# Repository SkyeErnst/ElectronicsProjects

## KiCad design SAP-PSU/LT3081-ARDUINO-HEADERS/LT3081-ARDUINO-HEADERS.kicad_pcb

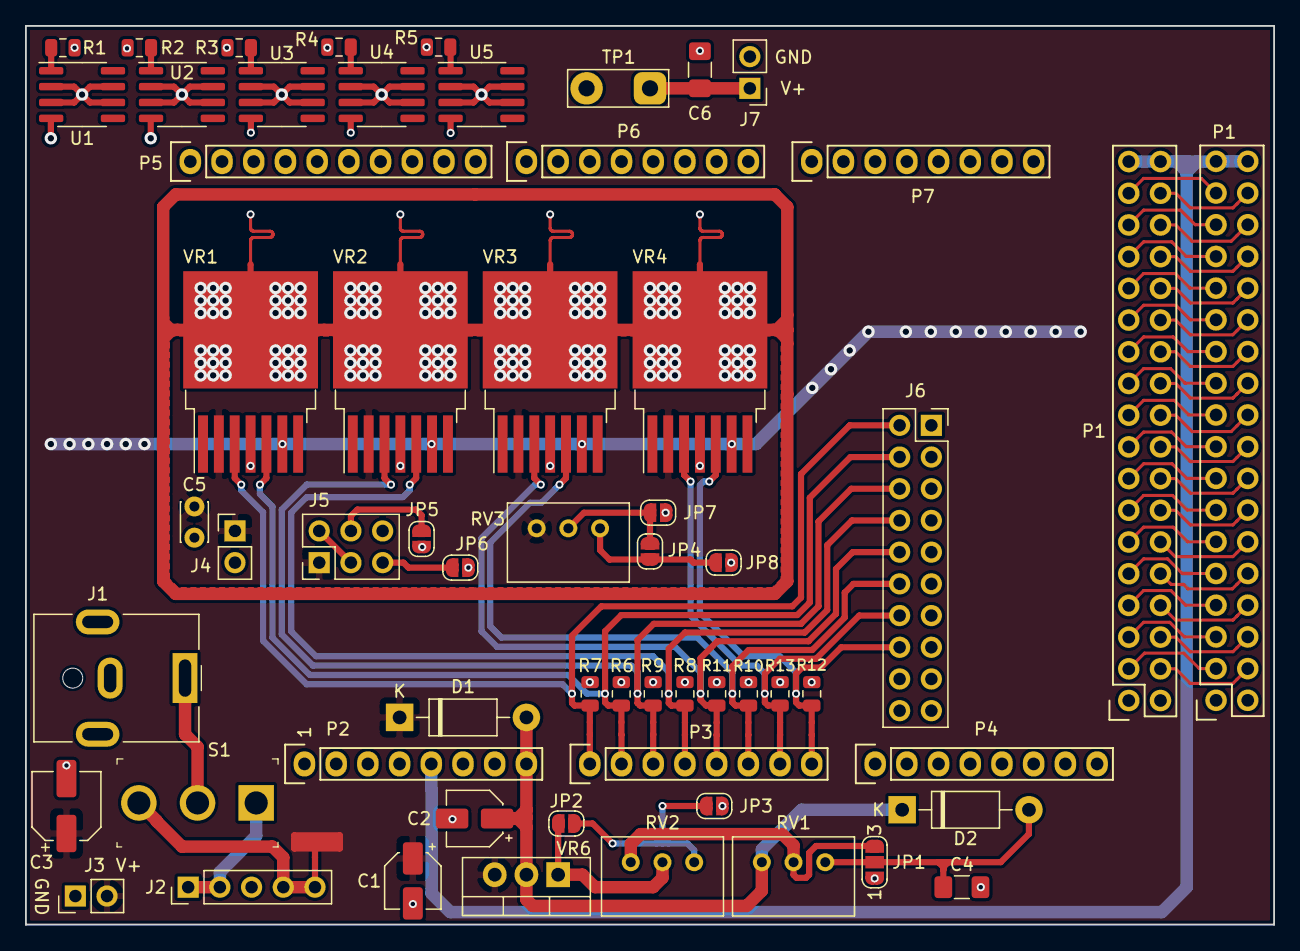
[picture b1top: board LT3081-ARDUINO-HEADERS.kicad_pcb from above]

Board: 4 copper layers, 100.0 x 72.0 mm, 72 parts (0 on the bottom side), 72 nets.

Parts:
C1, C2: 1uF; CP_Elec_4x4.5
C3: 10uF; CP_Elec_5x5.3
C4, C6: 10uF; C_1206_3216Metric_Pad1.42x1.75mm_HandSolder
C5: 10pF; C_Disc_D3.0mm_W2.0mm_P2.50mm
D1, D2: 1N4002; D_DO-41_SOD81_P10.16mm_Horizontal
J1: Barrel_Jack; BarrelJack_CUI_PJ-063AH_Horizontal
J2: Current monitor / direct switcher; PinHeader_1x05_P2.54mm_Vertical
J3: pwr_con; PinHeader_1x02_P2.54mm_Vertical
J4: Res_Bypass; PinHeader_1x02_P2.54mm_Vertical
J5: RV Header; PinHeader_2x03_P2.54mm_Vertical
J6: Sensor Header; PinSocket_2x10_P2.54mm_Vertical
J7: pwr_out_con; PinHeader_1x02_P2.54mm_Vertical
JP1: Jumper_3_Open; SolderJumper-3_P1.3mm_Open_RoundedPad1.0x1.5mm_NumberLabels
JP2, JP3, JP4, JP7, JP8: Jumper_NO_Small; SolderJumper-2_P1.3mm_Open_RoundedPad1.0x1.5mm
JP5, JP6: Solder Jumper; SolderJumper-2_P1.3mm_Open_RoundedPad1.0x1.5mm
NT1, NT2, NT3, NT4, NT5, NT6, NT7, NT8, NT9, NT10, NT11, NT14, NT15: Net-Tie_2; NetTie-2_SMD_Pad0.5mm
P1, P1#2: Digital; Socket_Strip_Arduino_2x18
P2: Power; Socket_Strip_Arduino_1x08
P3, P4: Analog; Socket_Strip_Arduino_1x08
P5: PWM; Socket_Strip_Arduino_1x10
P6: PWM; Socket_Strip_Arduino_1x08
P7: Communication; Socket_Strip_Arduino_1x08
R1, R2, R3, R4, R5: 47; R_0805_2012Metric
R6, R7, R8, R9, R10, R11, R12, R13: 1k; R_0805_2012Metric
RV1, RV2: 0-5k; Potentiometer_Bourns_3299W_Vertical
RV3: 0-250k; Potentiometer_Bourns_3299W_Vertical
S1: 100SP1T1B4M2QE; Toggle_Switch_100SP1T1B4M2QE
TP1: TestPoint_2Pole; TestPoint_2Pads_Pitch5.08mm_Drill1.3mm
U1, U2, U3, U4, U5: LM334M; SOIC-8_3.9x4.9mm_P1.27mm
VR1, VR2, VR3, VR4: LT3081ER-PBF; TO-263-7_TabPin8
VR6: LM317T; TO-220-3_Vertical

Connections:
+5V: P1.35, P1.36, P1#2.35, P1#2.36, P2.5
+12V: J2.4, J2.5, NT1.2, S1.3
/22: P1.33, P1#2.33
/23: P1.34, P1#2.34
/24: P1.31, P1#2.31
/25: P1.32, P1#2.32
/26: P1.29, P1#2.29
/27: P1.30, P1#2.30
/28: P1.27, P1#2.27
/29: P1.28, P1#2.28
/30: P1.25, P1#2.25
/31: P1.26, P1#2.26
/32: P1.23, P1#2.23
/33: P1.24, P1#2.24
/34: P1.21, P1#2.21
/35: P1.22, P1#2.22
/36: P1.19, P1#2.19
/37: P1.20, P1#2.20
/38: P1.17, P1#2.17
/39: P1.18, P1#2.18
/40: P1.15, P1#2.15
/41: P1.16, P1#2.16
/42: P1.13, P1#2.13
/43: P1.14, P1#2.14
/44: P1.11, P1#2.11
/45: P1.12, P1#2.12
/46: P1.9, P1#2.9
/47: P1.10, P1#2.10
/48: P1.7, P1#2.7
/49: P1.8, P1#2.8
/50(MISO): P1.5, P1#2.5
/51(MOSI): P1.6, P1#2.6
/52(SCK): P1.3, P1#2.3
/53(SS): P1.4, P1#2.4
/A0: NT3.2, P3.1
/A1: NT4.2, P3.2
/A2: NT5.2, P3.3
/A3: NT6.2, P3.4
/A4: NT7.2, P3.5
/A5: NT8.2, P3.6
/A6: NT10.2, P3.7
/A7: NT11.2, P3.8
/ImonVR1: J6.2, NT3.1, R7.1, VR1.3
/ImonVR2: J6.6, NT5.1, R9.1, VR2.3
/ImonVR3: J6.10, NT7.1, R11.1, VR3.3
/ImonVR4: J6.14, NT10.1, R13.1, VR4.3
/SET: C5.1, J4.1, J5.1, RV3.3, VR1.2, VR2.2, VR3.2, VR4.2
/TEMP1: J6.4, NT4.1, R6.1, VR1.5
/TEMP2: J6.8, NT6.1, R8.1, VR2.5
/TEMP3: J6.12, NT8.1, R10.1, VR3.5
/TEMP4: J6.16, NT11.1, R12.1, VR4.5
/VR_PAD: NT2.1, NT9.1, NT14.1, NT15.1, VR1.8, VR2.8, VR3.8, VR4.8
/Vin: C2.1, D1.2, D2.1, P2.8, RV1.3, VR6.2
/in: C1.1, C3.1, D1.1, J3.2, NT1.1, VR1.6, VR2.6, VR3.6, VR4.6, VR6.3
/out: C6.1, J7.1, NT2.2, NT9.2, NT14.2, NT15.2, TP1.1, U1.4, U2.4, U3.4, U4.4, U5.4, VR1.4, VR2.4, VR3.4, VR4.4
GND: C1.2, C2.2, C3.2, C4.2, C5.2, C6.2, J1.2, J3.1, J4.2, J5.6, J6.1, J6.3, J6.5, J6.7, J6.9, J6.11, J6.13, J6.15, J6.17, J6.19, J7.2, JP1.1, JP3.2, JP5.2, JP6.2, JP7.2, JP8.1, P1.1, P1.2, P1#2.1, P1#2.2, P2.6, P2.7, P5.4, R1.2, R2.2, R3.2, R4.2, R5.2, R6.2, R7.2, R8.2, R9.2, R10.2, R11.2, R12.2, R13.2, TP1.2, U1.2, U1.3, U1.6, U1.7, U2.2, U2.3, U2.6, U2.7, U3.2, U3.3, U3.6, U3.7, U4.2, U4.3, U4.6, U4.7, U5.2, U5.3, U5.6, U5.7
unnamed: C4.1, D2.2, JP1.2, RV1.1
unnamed: J1.1, S1.2
unnamed: J2.1, J2.2, S1.1
unnamed: J5.2, J5.3
unnamed: J5.4, JP5.1
unnamed: J5.5, JP6.1
unnamed: JP1.3, RV1.2, RV2.3
unnamed: JP2.1, RV2.2, VR6.1
unnamed: JP2.2, JP3.1, RV2.1
unnamed: JP4.1, JP8.2, RV3.1
unnamed: JP4.2, JP7.1, RV3.2
unnamed: R1.1, U1.1
unnamed: R2.1, U2.1
unnamed: R3.1, U3.1
unnamed: R4.1, U4.1
unnamed: R5.1, U5.1

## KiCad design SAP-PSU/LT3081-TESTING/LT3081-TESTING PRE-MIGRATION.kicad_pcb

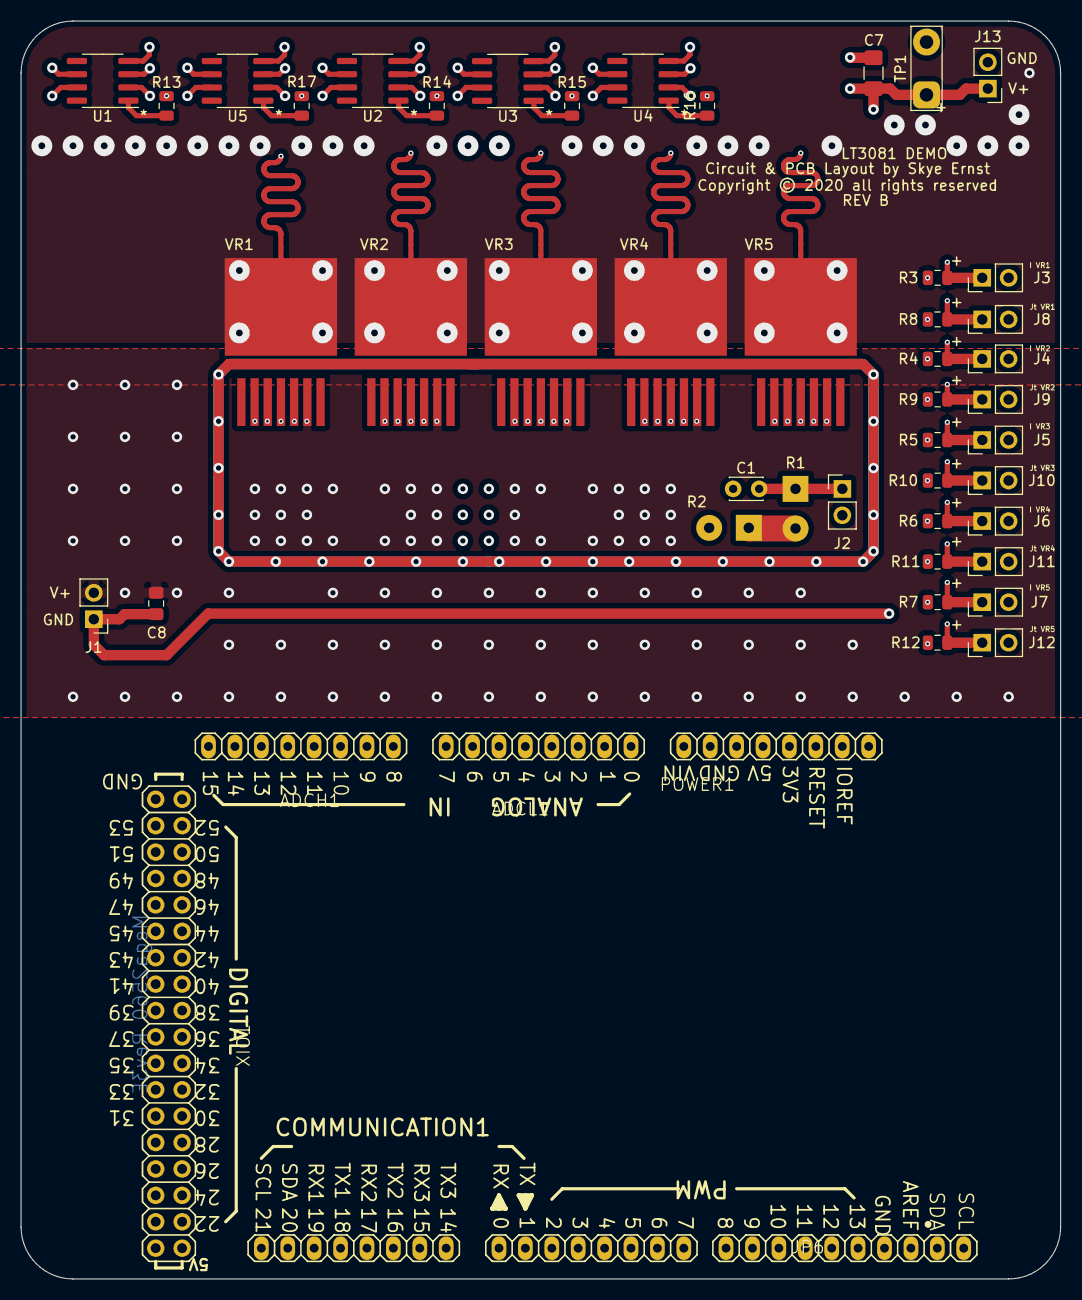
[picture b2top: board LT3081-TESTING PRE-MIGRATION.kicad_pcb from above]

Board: 4 copper layers, 100.0 x 121.0 mm, 56 parts (0 on the bottom side), 21 nets.

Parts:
ADCH1: FH254-108DF08500V; 1X08
ADCL1: FH254-108DF08500V; 1X08
C1: 10pF; C_Disc_D3.0mm_W2.0mm_P2.50mm
C7: 10uF; C_1206_3216Metric_Pad1.42x1.75mm_HandSolder
C8: 1uF; C_0805_2012Metric_Pad1.15x1.40mm_HandSolder
COMMUNICATION1: FH254-108DF08500V; 1X08
J1, J13: pwr_con; PinHeader_1x02_P2.54mm_Vertical
J2: Res_Bypass; PinHeader_1x02_P2.54mm_Vertical
J3, J4, J5, J6, J7: Imon; PinHeader_1x02_P2.54mm_Vertical
J8, J9, J10, J11, J12: temp; PinHeader_1x02_P2.54mm_Vertical
JP6: FH254-110DF08500V; 1X10
NT1, NT2, NT3, NT4, NT5: Net-Tie_2; NetTie-2_SMD_Pad0.5mm
POWER1: FH254-108DF08500V; 1X08
PWML1: FH254-108DF08500V; 1X08
R1, R2: 150k; SolderWirePad_1x02_P3.81mm_Drill1mm
R3, R4, R5, R6, R7, R8, R9, R10, R11, R12: 1k; R_0805_2012Metric
R13, R14, R15, R16, R17: 47; R_0805_2012Metric
TP1: TestPoint_2Pole; TestPoint_2Pads_Pitch5.08mm_Drill1.3mm
U1, U2, U3, U4, U5: LM334M; SOIC-8_3.9x4.9mm_P1.27mm
VR1, VR2, VR3, VR4, VR5: LT3081ER-PBF; TO-263-7_TabPin8
XIO1: 18x2F-H8.5; 2X18

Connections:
/ImonVR1: J3.1, R3.1, VR1.3
/ImonVR2: J4.1, R4.1, VR2.3
/ImonVR3: J5.1, R5.1, VR3.3
/ImonVR4: J6.1, R6.1, VR4.3
/ImonVR5: J7.1, R7.1, VR5.3
/SET: C1.1, J2.1, R1.1, VR1.2, VR2.2, VR3.2, VR4.2, VR5.2
/TEMP1: J8.1, R8.1, VR1.5
/TEMP2: J9.1, R9.1, VR2.5
/TEMP3: J10.1, R10.1, VR3.5
/TEMP4: J11.1, R11.1, VR4.5
/TEMP5: J12.1, R12.1, VR5.5
/VR_PAD: NT1.1, NT2.1, NT3.1, NT4.1, NT5.1, VR1.8, VR2.8, VR3.8, VR4.8, VR5.8
/in: C8.1, J1.2, VR1.6, VR2.6, VR3.6, VR4.6, VR5.6
/out: C7.1, J13.1, NT1.2, NT2.2, NT3.2, NT4.2, NT5.2, TP1.1, U1.4, U2.4, U3.4, U4.4, U5.4, VR1.4, VR2.4, VR3.4, VR4.4, VR5.4
GND: C1.2, C7.2, C8.2, J1.1, J2.2, J3.2, J4.2, J5.2, J6.2, J7.2, J8.2, J9.2, J10.2, J11.2, J12.2, J13.2, R2.2, R3.2, R4.2, R5.2, R6.2, R7.2, R8.2, R9.2, R10.2, R11.2, R12.2, R13.2, R14.2, R15.2, R16.2, R17.2, TP1.2, U1.2, U1.3, U1.6, U1.7, U2.2, U2.3, U2.6, U2.7, U3.2, U3.3, U3.6, U3.7, U4.2, U4.3, U4.6, U4.7, U5.2, U5.3, U5.6, U5.7
unnamed: R1.2, R2.1
unnamed: R13.1, U1.1
unnamed: R14.1, U2.1
unnamed: R15.1, U3.1
unnamed: R16.1, U4.1
unnamed: R17.1, U5.1

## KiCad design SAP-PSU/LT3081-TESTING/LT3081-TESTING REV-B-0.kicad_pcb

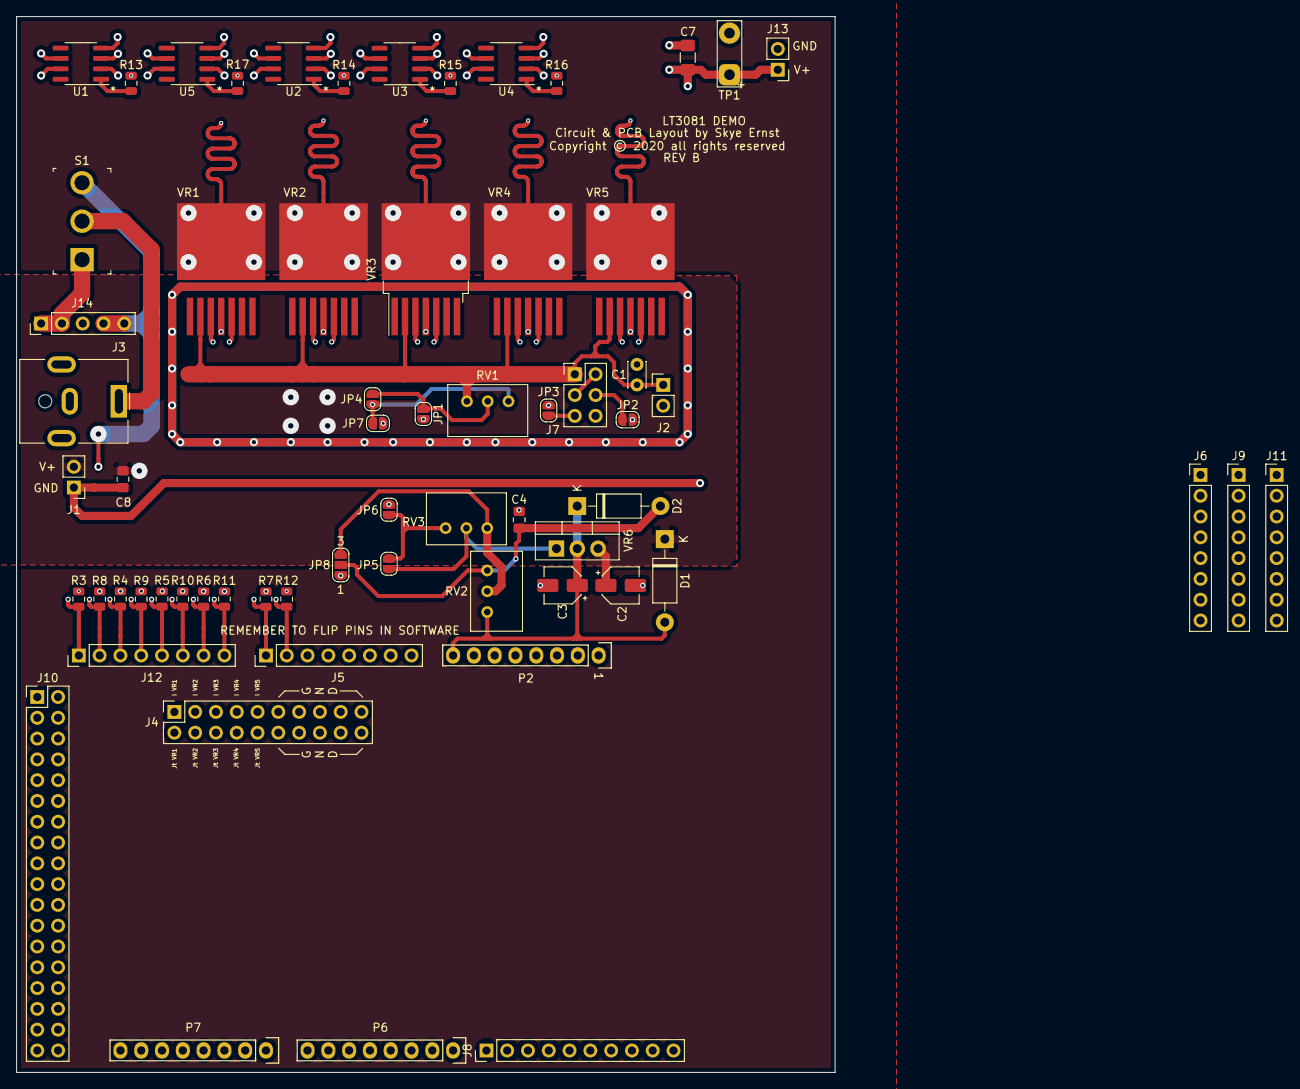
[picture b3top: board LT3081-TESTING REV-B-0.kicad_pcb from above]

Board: 4 copper layers, 100.0 x 129.0 mm, 80 parts (0 on the bottom side), 45 nets.

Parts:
C1: 10pF; C_Disc_D3.0mm_W2.0mm_P2.50mm
C2, C3: 1uF; CP_Elec_4x5.8
C4, C8: 10uF; C_0805_2012Metric_Pad1.15x1.40mm_HandSolder
C7: 10uF; C_1206_3216Metric_Pad1.42x1.75mm_HandSolder
D1, D2: 1N4002; D_DO-41_SOD81_P10.16mm_Horizontal
J1, J13: pwr_con; PinHeader_1x02_P2.54mm_Vertical
J2: Res_Bypass; PinHeader_1x02_P2.54mm_Vertical
J3: Barrel_Jack; BarrelJack_CUI_PJ-063AH_Horizontal
J4: Sensor Header; PinSocket_2x10_P2.54mm_Vertical
J5, J6, J9, J11, J12: FH254-108DF08500V; PinHeader_1x08_P2.54mm_Vertical
J7: RV Header; PinHeader_2x03_P2.54mm_Vertical
J8: FH254-110DF08500V; PinHeader_1x10_P2.54mm_Vertical
J10: 18x2F-H8.5; PinHeader_2x18_P2.54mm_Vertical
J14: Current monitor / direct switcher; PinHeader_1x05_P2.54mm_Vertical
JP1, JP4, JP5, JP6, JP7: Jumper_NO_Small; SolderJumper-2_P1.3mm_Open_RoundedPad1.0x1.5mm
JP2, JP3: Solder Jumper; SolderJumper-2_P1.3mm_Open_RoundedPad1.0x1.5mm
JP8: Jumper_3_Open; SolderJumper-3_P1.3mm_Open_RoundedPad1.0x1.5mm_NumberLabels
NT1, NT2, NT3, NT4, NT5, NT6, NT7, NT8, NT9, NT10, NT11, NT12, NT13, NT14, NT15, NT16: Net-Tie_2; NetTie-2_SMD_Pad0.5mm
P2: Power; Socket_Strip_Arduino_1x08
P6: PWM; Socket_Strip_Arduino_1x08
P7: Communication; Socket_Strip_Arduino_1x08
R3, R4, R5, R6, R7, R8, R9, R10, R11, R12: 1k; R_0805_2012Metric
R13, R14, R15, R16, R17: 47; R_0805_2012Metric
RV1: 0-250k; Potentiometer_Bourns_3299W_Vertical
RV2, RV3: 0-5k; Potentiometer_Bourns_3299W_Vertical
S1: 100SP1T1B4M2QE; Toggle_Switch_100SP1T1B4M2QE
TP1: TestPoint_2Pole; TestPoint_2Pads_Pitch5.08mm_Drill1.3mm
U1, U2, U3, U4, U5: LM334M; SOIC-8_3.9x4.9mm_P1.27mm
VR1, VR2, VR3, VR4, VR5: LT3081ER-PBF; TO-263-7_TabPin8
VR6: LM317T; TO-220-3_Vertical

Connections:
+5V: C3.1, D1.2, D2.1, J6.2, J6.5, J10.1, J10.2, P2.8, RV2.3, VR6.2
+12V: J14.4, J14.5, NT6.2, S1.3
/Digital/ADC0: J12.1, NT9.2
/Digital/ADC1: J12.2, NT13.2
/Digital/ADC2: J12.3, NT10.2
/Digital/ADC3: J12.4, NT14.2
/Digital/ADC4: J12.5, NT11.2
/Digital/ADC5: J12.6, NT15.2
/Digital/ADC6: J12.7, NT12.2
/Digital/ADC7: J12.8, NT16.2
/Digital/ADC8: J5.1, NT7.2
/Digital/ADC9: J5.2, NT8.2
/Digital/SCL: J8.1, J9.1
/Digital/SDA: J8.2, J9.2
/ImonVR1: J4.1, NT9.1, R3.1, VR1.3
/ImonVR2: J4.3, NT10.1, R4.1, VR2.3
/ImonVR3: J4.5, NT11.1, R5.1, VR3.3
/ImonVR4: J4.7, NT12.1, R6.1, VR4.3
/ImonVR5: J4.9, NT7.1, R7.1, VR5.3
/SET: C1.1, J2.1, J7.1, RV1.3, VR1.2, VR2.2, VR3.2, VR4.2, VR5.2
/TEMP1: J4.2, NT13.1, R8.1, VR1.5
/TEMP2: J4.4, NT14.1, R9.1, VR2.5
/TEMP3: J4.6, NT15.1, R10.1, VR3.5
/TEMP4: J4.8, NT16.1, R11.1, VR4.5
/TEMP5: J4.10, NT8.1, R12.1, VR5.5
/VR_PAD: NT1.1, NT2.1, NT3.1, NT4.1, NT5.1, VR1.8, VR2.8, VR3.8, VR4.8, VR5.8
/in: C2.1, C8.1, D1.1, J1.2, J6.8, NT6.1, VR1.6, VR2.6, VR3.6, VR4.6, VR5.6, VR6.3
/out: C7.1, J13.1, NT1.2, NT2.2, NT3.2, NT4.2, NT5.2, TP1.1, U1.4, U2.4, U3.4, U4.4, U5.4, VR1.4, VR2.4, VR3.4, VR4.4, VR5.4
GND: C1.2, C2.2, C3.2, C4.2, C7.2, C8.2, J1.1, J2.2, J3.2, J4.11, J4.12, J4.13, J4.14, J4.15, J4.16, J4.17, J4.18, J4.19, J4.20, J6.6, J6.7, J7.6, J8.4, J10.35, J10.36, J13.2, JP1.2, JP2.2, JP3.2, JP6.2, JP7.1, JP8.1, R3.2, R4.2, R5.2, R6.2, R7.2, R8.2, R9.2, R10.2, R11.2, R12.2, R13.2, R14.2, R15.2, R16.2, R17.2, TP1.2, U1.2, U1.3, U1.6, U1.7, U2.2, U2.3, U2.6, U2.7, U3.2, U3.3, U3.6, U3.7, U4.2, U4.3, U4.6, U4.7, U5.2, U5.3, U5.6, U5.7
unnamed: C4.1, D2.2, JP8.2, RV2.1
unnamed: J3.1, S1.2
unnamed: J7.2, J7.3
unnamed: J7.4, JP2.1
unnamed: J7.5, JP3.1
unnamed: J14.1, J14.2, S1.1
unnamed: JP1.1, JP4.2, RV1.2
unnamed: JP4.1, JP7.2, RV1.1
unnamed: JP5.1, RV3.2, VR6.1
unnamed: JP5.2, JP6.1, RV3.1
unnamed: JP8.3, RV2.2, RV3.3
unnamed: R13.1, U1.1
unnamed: R14.1, U2.1
unnamed: R15.1, U3.1
unnamed: R16.1, U4.1
unnamed: R17.1, U5.1

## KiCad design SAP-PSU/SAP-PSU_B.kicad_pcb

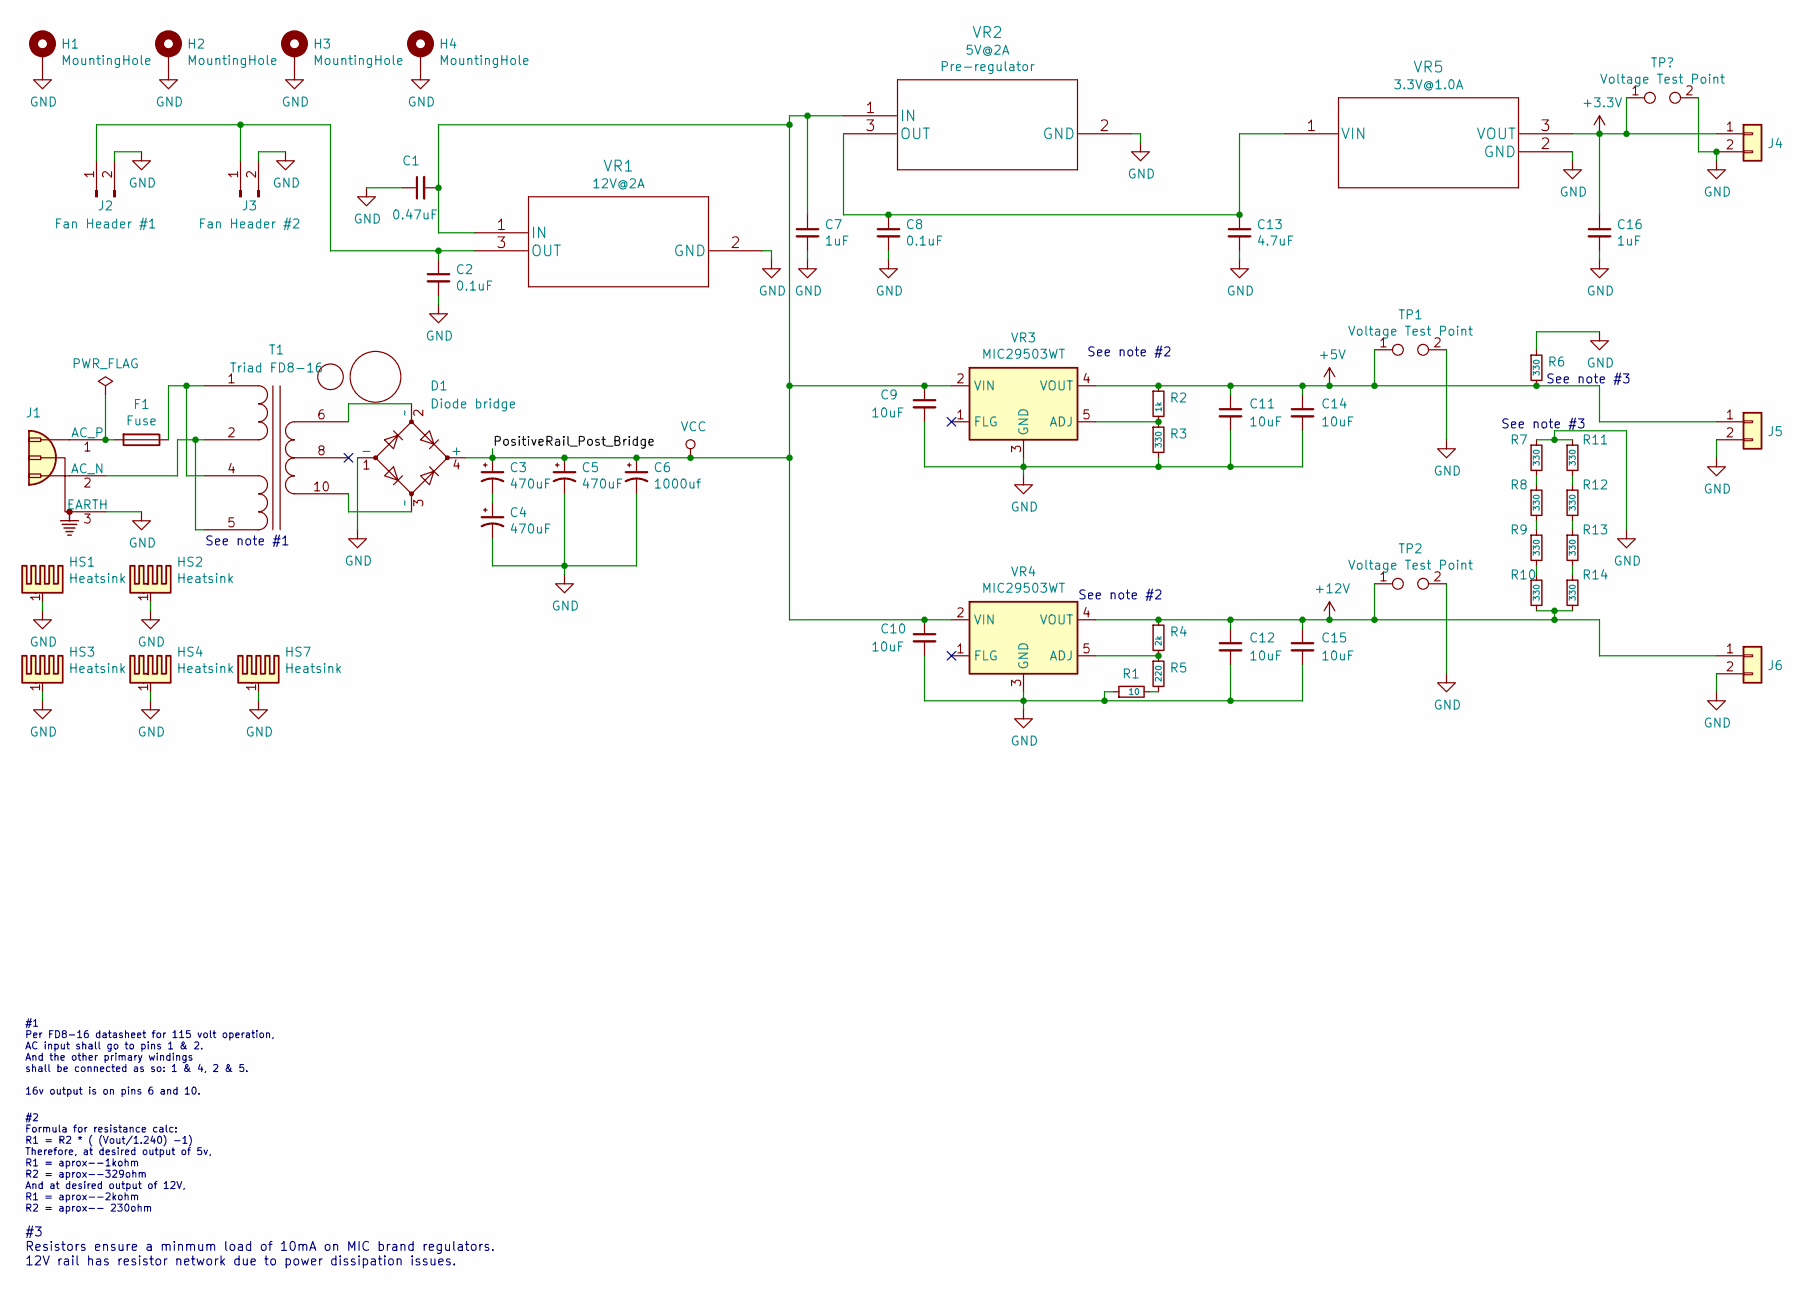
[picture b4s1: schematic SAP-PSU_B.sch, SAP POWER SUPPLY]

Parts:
C1: 0.47uF; C_0805_2012Metric_Pad1.15x1.40mm_HandSolder; digikey 1276-1039-1-ND
C2, C8: 0.1uF; C_0805_2012Metric_Pad1.15x1.40mm_HandSolder; digikey 1276-2450-1-ND
C3, C4, C5: 470uF; CP_Radial_D10.0mm_P5.00mm; digikey 1189-1407-ND
C6: 1000uf; CP_Radial_D12.5mm_P5.00mm; digikey 493-12914-1-ND
C7: 1uF; C_0805_2012Metric_Pad1.15x1.40mm_HandSolder; digikey 1276-1039-1-ND
C9, C10, C11, C12, C14, C15: 10uF; C_0805_2012Metric_Pad1.15x1.40mm_HandSolder
C13: 4.7uF; C_1206_3216Metric_Pad1.42x1.75mm_HandSolder; digikey 1276-2789-1-ND
C16: 1uF; C_0805_2012Metric_Pad1.15x1.40mm_HandSolder; digikey 1276-6470-1-ND
D1: Diode bridge; Diode_Bridge_Vishay_GBU; digikey GBU606TB
F1: Fuse; Fuseholder_Cylinder-5x20mm_Schurter_0031_8201_Horizontal_Op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
H1, H2, H3, H4: MountingHole; MountingHole_3.2mm_M3_Pad
HS1, HS2, HS3, HS4, HS7: Heatsink; Bigger_TO220_Heatsink
J1: Conn_WallSocket_Earth; Banana_Jack_3Pin
J2: Fan Header #1; PinHeader_1x02_P2.54mm_Vertical
J3: Fan Header #2; PinHeader_1x02_P2.54mm_Vertical
J4, J5, J6: Conn_01x02; SolderWirePad_1x02_P3.81mm_Drill1mm; digikey red J10125-ND
R1: 10; R_Axial_DIN0207_L6.3mm_D2.5mm_P15.24mm_Horizontal
R2: 1k; R_Axial_DIN0207_L6.3mm_D2.5mm_P15.24mm_Horizontal
R3, R6, R7, R8, R9, R10, R11, R12, R13, R14: 330; R_Axial_DIN0207_L6.3mm_D2.5mm_P15.24mm_Horizontal
R4: 2k; R_Axial_DIN0207_L6.3mm_D2.5mm_P15.24mm_Horizontal
R5: 220; R_Axial_DIN0207_L6.3mm_D2.5mm_P15.24mm_Horizontal
T1: Triad FD8-16; TriadTransformer; digikey FD8-16
TP1, TP2: Voltage Test Point; TestPoint_2Pads_Pitch5.08mm_Drill1.3mm
VR1: L78S12CV; TO-220-3_Vertical; Rating: 12V@2A
VR2: L78S05CV; TO-220-3_Vertical; Rating 5V@2A
VR3, VR4: MIC29503WT; TO-220-5_Vertical
VR5: MCP1826S-3302E_AB; TO-220-3_Vertical; Rating 3.3V@1.0A

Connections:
+3V3: C16.1, J4.1, VR5.3 (VOUT)
+5V: C11.1, C14.1, J5.1, R2.1, R6.2, TP1.1, VR3.4 (VOUT)
+12V: C12.1, C15.1, J6.1, R4.1, R10.2, R14.2, TP2.1, VR4.4 (VOUT)
GND: C1.1, C2.2, C4.2, C5.2, C6.2, C7.2, C8.2, C9.2, C10.2, C11.2, C12.2, C13.2, C14.2, C15.2, C16.2, D1.1 (-), H1.1, H2.1, H3.1, H4.1, HS1.1, HS2.1, HS3.1, HS4.1, HS7.1, J1.3 (EARTH), J2.2, J3.2, J4.2, J5.2, J6.2, R1.1, R3.2, R6.1, R7.1, R11.1, TP1.2, TP2.2, VR1.2 (GND), VR2.2 (GND), VR3.3 (GND), VR4.3 (GND), VR5.2 (GND)
unnamed: C2.1, J2.1, J3.1, VR1.3 (OUT)
unnamed: C3.2, C4.1
unnamed: C8.1, C13.1, VR2.3 (OUT), VR5.1 (VIN)
unnamed: D1.2 (~~), T1.6 (IN+)
unnamed: D1.3 (~~), T1.10 (IN-)
unnamed: F1.1, T1.1 (OUT1A), T1.4 (OUT2A)
unnamed: F1.2, J1.1 (AC_P)
unnamed: J1.2 (AC_N), T1.2 (OUT1B), T1.5 (OUT2B)
unnamed: R1.2, R5.2
unnamed: R2.2, R3.1, VR3.5 (ADJ)
unnamed: R4.2, R5.1, VR4.5 (ADJ)
unnamed: R7.2, R8.1
unnamed: R8.2, R9.1
unnamed: R9.2, R10.1
unnamed: R11.2, R12.1
unnamed: R12.2, R13.1
unnamed: R13.2, R14.1
VCC: C1.2, C3.1, C5.1, C6.1, C7.1, C9.1, C10.1, D1.4 (+), VR1.1 (IN), VR2.1 (IN), VR3.2 (VIN), VR4.2 (VIN)

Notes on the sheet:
See note #1
#1 Per FD8-16 datasheet for 115 volt operation, AC input shall go to pins 1 & 2. And the other primary windings shall be connected as so: 1 & 4, 2 & 5. 16v output is on pins 6 and 10.
See note #2
#2 Formula for resistance calc: R1 = R2 * ( (Vout/1.240) -1) Therefore, at desired output of 5v, R1 = aprox--1kohm R2 = aprox--329ohm And at desired output of 12V, R1 = aprox--2kohm R2 = aprox-- 230ohm
See note #3
#3 Resistors ensure a minmum load of 10mA on MIC brand regulators. 12V rail has resistor network due to power dissipation issues.

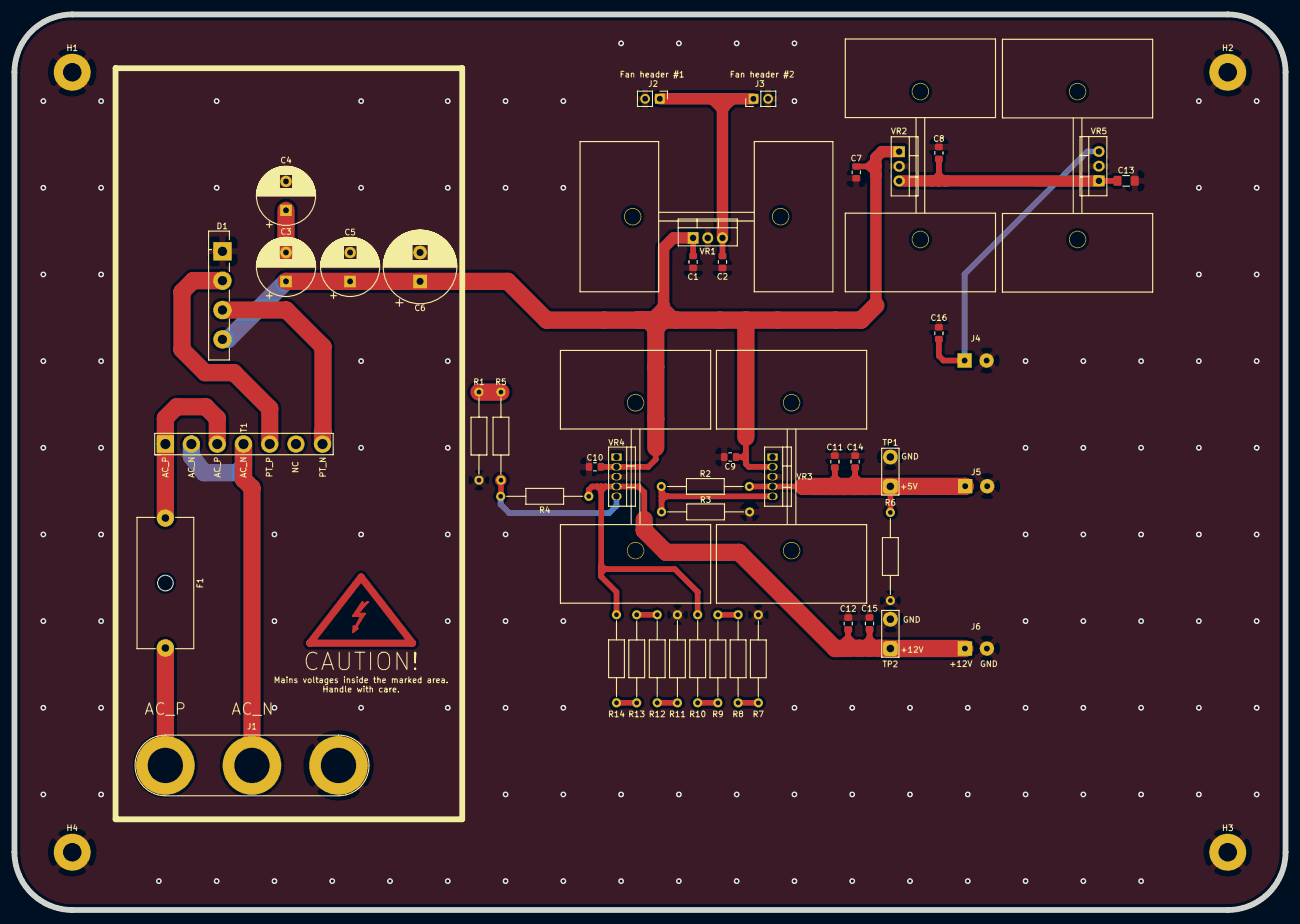
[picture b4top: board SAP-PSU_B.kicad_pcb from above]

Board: 2 copper layers, 220.0 x 155.0 mm, 55 parts (0 on the bottom side), 22 nets.

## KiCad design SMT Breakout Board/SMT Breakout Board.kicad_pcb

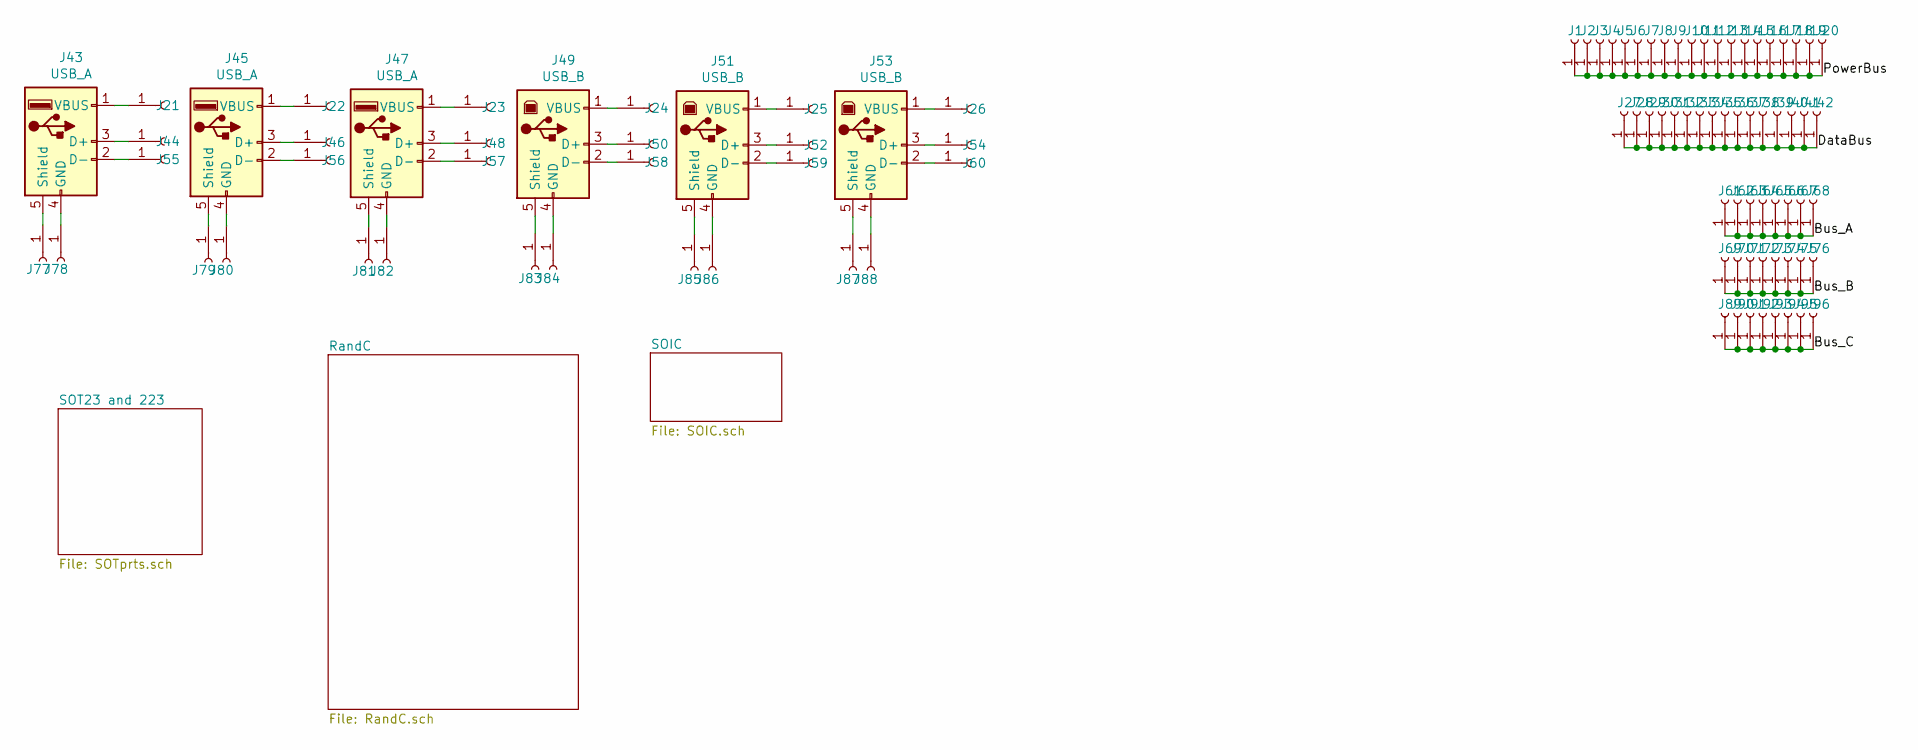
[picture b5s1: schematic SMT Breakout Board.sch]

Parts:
J1, J2, J3, J4, J5, J6, J7, J8, J9, J10, J11, J12, J13, J14, J15, J16, J17, J18, J19, J20, J21, J22, J23, J24, J25, J26, J27, J28, J29, J30, J31, J32, J33, J34, J35, J36, J37, J38, J39, J40, J41, J42, J44, J46, J48, J50, J52, J54, J55, J56, J57, J58, J59, J60, J61, J62, J63, J64, J65, J66, J67, J68, J69, J70, J71, J72, J73, J74, J75, J76, J77, J78, J79, J80, J81, J82, J83, J84, J85, J86, J87, J88, J89, J90, J91, J92, J93, J94, J95, J96: Conn_01x01_Female; PinSocket_1x01_P2.00mm_Vertical
J43, J45, J47: USB_A; USB_A_CNCTech_1001-011-01101_Horizontal
J49, J51, J53: USB_B; USB_B_OST_USB-B1HSxx_Horizontal

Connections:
/Bus_A: J61.1, J62.1, J63.1, J64.1, J65.1, J66.1, J67.1, J68.1
/Bus_B: J69.1, J70.1, J71.1, J72.1, J73.1, J74.1, J75.1, J76.1
/Bus_C: J89.1, J90.1, J91.1, J92.1, J93.1, J94.1, J95.1, J96.1
/DataBus: J27.1, J28.1, J29.1, J30.1, J31.1, J32.1, J33.1, J34.1, J35.1, J36.1, J37.1, J38.1, J39.1, J40.1, J41.1, J42.1
/PowerBus: J1.1, J2.1, J3.1, J4.1, J5.1, J6.1, J7.1, J8.1, J9.1, J10.1, J11.1, J12.1, J13.1, J14.1, J15.1, J16.1, J17.1, J18.1, J19.1, J20.1
unnamed: J21.1, J43.1 (VBUS)
unnamed: J22.1, J45.1 (VBUS)
unnamed: J23.1, J47.1 (VBUS)
unnamed: J24.1, J49.1 (VBUS)
unnamed: J25.1, J51.1 (VBUS)
unnamed: J26.1, J53.1 (VBUS)
unnamed: J43.2 (D-), J55.1
unnamed: J43.3 (D+), J44.1
unnamed: J43.4 (GND), J78.1
unnamed: J43.5 (Shield), J77.1
unnamed: J45.2 (D-), J56.1
unnamed: J45.3 (D+), J46.1
unnamed: J45.4 (GND), J80.1
unnamed: J45.5 (Shield), J79.1
unnamed: J47.2 (D-), J57.1
unnamed: J47.3 (D+), J48.1
unnamed: J47.4 (GND), J82.1
unnamed: J47.5 (Shield), J81.1
unnamed: J49.2 (D-), J58.1
unnamed: J49.3 (D+), J50.1
unnamed: J49.4 (GND), J84.1
unnamed: J49.5 (Shield), J83.1
unnamed: J51.2 (D-), J59.1
unnamed: J51.3 (D+), J52.1
unnamed: J51.4 (GND), J86.1
unnamed: J51.5 (Shield), J85.1
unnamed: J53.2 (D-), J60.1
unnamed: J53.3 (D+), J54.1
unnamed: J53.4 (GND), J88.1
unnamed: J53.5 (Shield), J87.1

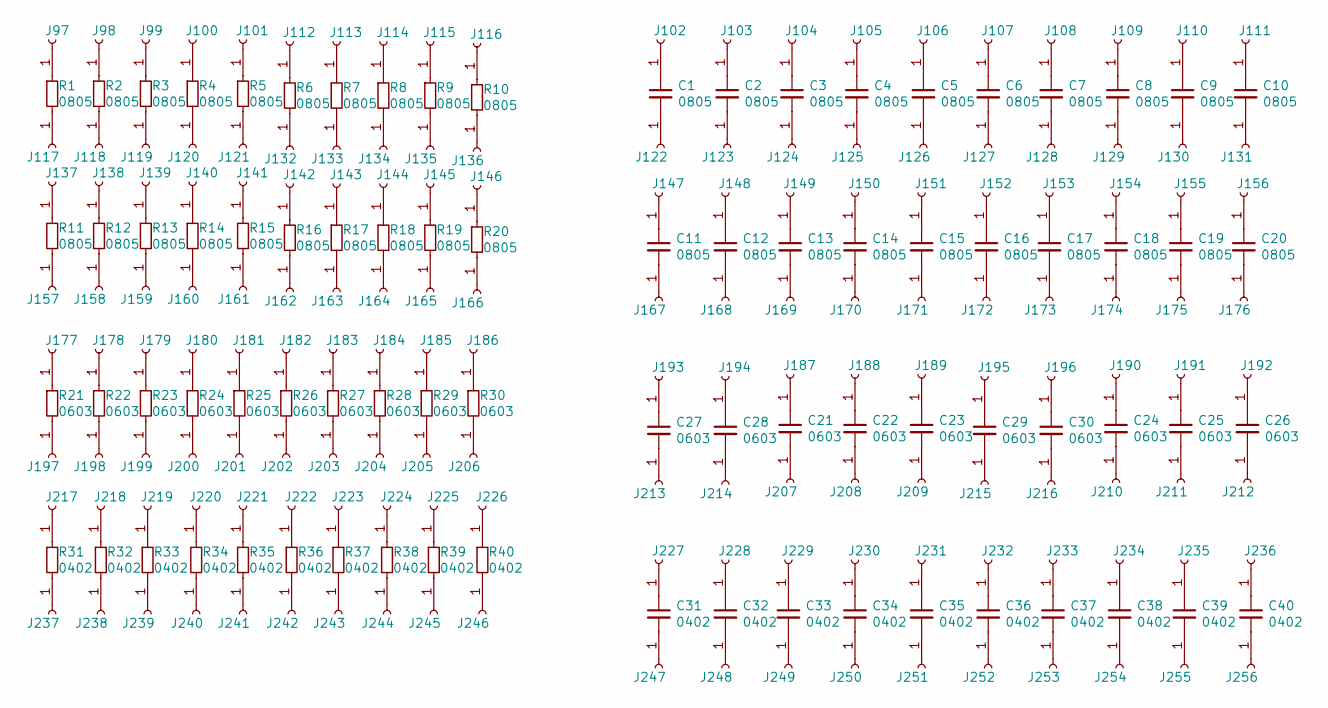
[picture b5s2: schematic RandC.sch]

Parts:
C1, C2, C3, C4, C5, C6, C7, C8, C9, C10, C11, C12, C13, C14, C15, C16, C17, C18, C19, C20: 0805; C_0805_2012Metric_Pad1.15x1.40mm_HandSolder
C21, C22, C23, C24, C25, C26, C27, C28, C29, C30: 0603; C_0603_1608Metric_Pad1.05x0.95mm_HandSolder
C31, C32, C33, C34, C35, C36, C37, C38, C39, C40: 0402; C_0402_1005Metric
J97, J98, J99, J100, J101, J102, J103, J104, J105, J106, J107, J108, J109, J110, J111, J112, J113, J114, J115, J116, J117, J118, J119, J120, J121, J122, J123, J124, J125, J126, J127, J128, J129, J130, J131, J132, J133, J134, J135, J136, J137, J138, J139, J140, J141, J142, J143, J144, J145, J146, J147, J148, J149, J150, J151, J152, J153, J154, J155, J156, J157, J158, J159, J160, J161, J162, J163, J164, J165, J166, J167, J168, J169, J170, J171, J172, J173, J174, J175, J176, J177, J178, J179, J180, J181, J182, J183, J184, J185, J186, J187, J188, J189, J190, J191, J192, J193, J194, J195, J196, J197, J198, J199, J200, J201, J202, J203, J204, J205, J206, J207, J208, J209, J210, J211, J212, J213, J214, J215, J216, J217, J218, J219, J220, J221, J222, J223, J224, J225, J226, J227, J228, J229, J230, J231, J232, J233, J234, J235, J236, J237, J238, J239, J240, J241, J242, J243, J244, J245, J246, J247, J248, J249, J250, J251, J252, J253, J254, J255, J256: Conn_01x01_Female; PinSocket_1x01_P2.00mm_Vertical
R1, R2, R3, R4, R5, R6, R7, R8, R9, R10, R11, R12, R13, R14, R15, R16, R17, R18, R19, R20: 0805; R_0805_2012Metric_Pad1.15x1.40mm_HandSolder
R21, R22, R23, R24, R25, R26, R27, R28, R29, R30: 0603; R_0603_1608Metric_Pad1.05x0.95mm_HandSolder
R31, R32, R33, R34, R35, R36, R37, R38, R39, R40: 0402; R_0402_1005Metric

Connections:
unnamed: C1.1, J102.1
unnamed: C1.2, J122.1
unnamed: C2.1, J103.1
unnamed: C2.2, J123.1
unnamed: C3.1, J104.1
unnamed: C3.2, J124.1
unnamed: C4.1, J105.1
unnamed: C4.2, J125.1
unnamed: C5.1, J106.1
unnamed: C5.2, J126.1
unnamed: C6.1, J107.1
unnamed: C6.2, J127.1
unnamed: C7.1, J108.1
unnamed: C7.2, J128.1
unnamed: C8.1, J109.1
unnamed: C8.2, J129.1
unnamed: C9.1, J110.1
unnamed: C9.2, J130.1
unnamed: C10.1, J111.1
unnamed: C10.2, J131.1
unnamed: C11.1, J147.1
unnamed: C11.2, J167.1
unnamed: C12.1, J148.1
unnamed: C12.2, J168.1
unnamed: C13.1, J149.1
unnamed: C13.2, J169.1
unnamed: C14.1, J150.1
unnamed: C14.2, J170.1
unnamed: C15.1, J151.1
unnamed: C15.2, J171.1
unnamed: C16.1, J152.1
unnamed: C16.2, J172.1
unnamed: C17.1, J153.1
unnamed: C17.2, J173.1
unnamed: C18.1, J154.1
unnamed: C18.2, J174.1
unnamed: C19.1, J155.1
unnamed: C19.2, J175.1
unnamed: C20.1, J156.1
unnamed: C20.2, J176.1
unnamed: C21.1, J187.1
unnamed: C21.2, J207.1
unnamed: C22.1, J188.1
unnamed: C22.2, J208.1
unnamed: C23.1, J189.1
unnamed: C23.2, J209.1
unnamed: C24.1, J190.1
unnamed: C24.2, J210.1
unnamed: C25.1, J191.1
unnamed: C25.2, J211.1
unnamed: C26.1, J192.1
unnamed: C26.2, J212.1
unnamed: C27.1, J193.1
unnamed: C27.2, J213.1
unnamed: C28.1, J194.1
unnamed: C28.2, J214.1
unnamed: C29.1, J195.1
unnamed: C29.2, J215.1
unnamed: C30.1, J196.1
unnamed: C30.2, J216.1
unnamed: C31.1, J227.1
unnamed: C31.2, J247.1
unnamed: C32.1, J228.1
unnamed: C32.2, J248.1
unnamed: C33.1, J229.1
unnamed: C33.2, J249.1
unnamed: C34.1, J230.1
unnamed: C34.2, J250.1
unnamed: C35.1, J231.1
unnamed: C35.2, J251.1
unnamed: C36.1, J232.1
unnamed: C36.2, J252.1
unnamed: C37.1, J233.1
unnamed: C37.2, J253.1
unnamed: C38.1, J234.1
unnamed: C38.2, J254.1
unnamed: C39.1, J235.1
unnamed: C39.2, J255.1
unnamed: C40.1, J236.1
unnamed: C40.2, J256.1
unnamed: J97.1, R1.1
unnamed: J98.1, R2.1
unnamed: J99.1, R3.1
unnamed: J100.1, R4.1
unnamed: J101.1, R5.1
unnamed: J112.1, R6.1
unnamed: J113.1, R7.1
unnamed: J114.1, R8.1
unnamed: J115.1, R9.1
unnamed: J116.1, R10.1
unnamed: J117.1, R1.2
unnamed: J118.1, R2.2
unnamed: J119.1, R3.2
unnamed: J120.1, R4.2
unnamed: J121.1, R5.2
unnamed: J132.1, R6.2
unnamed: J133.1, R7.2
unnamed: J134.1, R8.2
unnamed: J135.1, R9.2
unnamed: J136.1, R10.2
unnamed: J137.1, R11.1
unnamed: J138.1, R12.1
unnamed: J139.1, R13.1
unnamed: J140.1, R14.1
unnamed: J141.1, R15.1
unnamed: J142.1, R16.1
unnamed: J143.1, R17.1
unnamed: J144.1, R18.1
unnamed: J145.1, R19.1
unnamed: J146.1, R20.1
unnamed: J157.1, R11.2
unnamed: J158.1, R12.2
unnamed: J159.1, R13.2
unnamed: J160.1, R14.2
unnamed: J161.1, R15.2
unnamed: J162.1, R16.2
unnamed: J163.1, R17.2
unnamed: J164.1, R18.2
unnamed: J165.1, R19.2
unnamed: J166.1, R20.2
unnamed: J177.1, R21.1
unnamed: J178.1, R22.1
unnamed: J179.1, R23.1
unnamed: J180.1, R24.1
unnamed: J181.1, R25.1
unnamed: J182.1, R26.1
unnamed: J183.1, R27.1
unnamed: J184.1, R28.1
unnamed: J185.1, R29.1
unnamed: J186.1, R30.1
unnamed: J197.1, R21.2
unnamed: J198.1, R22.2
unnamed: J199.1, R23.2
unnamed: J200.1, R24.2
unnamed: J201.1, R25.2
unnamed: J202.1, R26.2
unnamed: J203.1, R27.2
unnamed: J204.1, R28.2
unnamed: J205.1, R29.2
unnamed: J206.1, R30.2
unnamed: J217.1, R31.1
unnamed: J218.1, R32.1
unnamed: J219.1, R33.1
unnamed: J220.1, R34.1
unnamed: J221.1, R35.1
unnamed: J222.1, R36.1
unnamed: J223.1, R37.1
unnamed: J224.1, R38.1
unnamed: J225.1, R39.1
unnamed: J226.1, R40.1
unnamed: J237.1, R31.2
unnamed: J238.1, R32.2
unnamed: J239.1, R33.2
unnamed: J240.1, R34.2
unnamed: J241.1, R35.2
unnamed: J242.1, R36.2
unnamed: J243.1, R37.2
unnamed: J244.1, R38.2
unnamed: J245.1, R39.2
unnamed: J246.1, R40.2

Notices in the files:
SAP-PSU/LT3081-TESTING/LT3081-TESTING PRE-MIGRATION.kicad_pcb:
Copyright © 2020 all rights reserved
